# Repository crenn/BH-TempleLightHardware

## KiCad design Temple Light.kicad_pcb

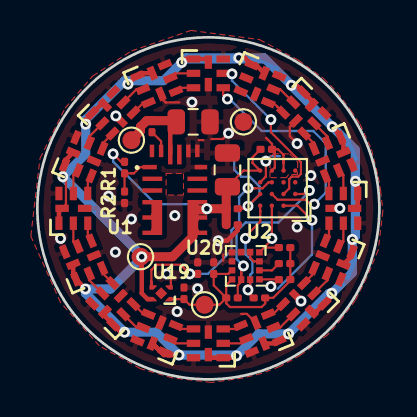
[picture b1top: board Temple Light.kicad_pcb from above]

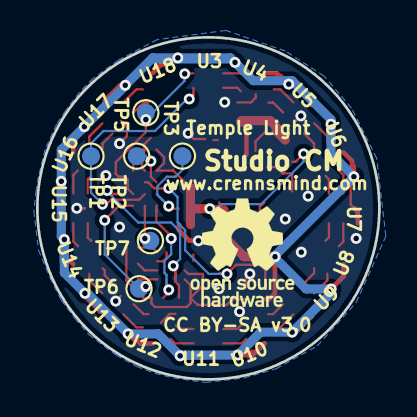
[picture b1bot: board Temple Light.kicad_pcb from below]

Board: 2 copper layers, 19.0 x 19.0 mm, 46 parts (6 on the bottom side), 47 nets.

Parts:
C1, C4, C5: 100NF; C_0201_0603Metric
C2: 10UF/25V; C_0805_2012Metric
C3: 47UF/6V3; C_0805_2012Metric
C6: 1UF; C_0201_0603Metric
R1, R3, R6, R7, R8, R9: 24K9; R_0201_0603Metric
R2, R4, R5: 4K7; R_0201_0603Metric
R10: 180K; R_0201_0603Metric
TP1, TP2, TP3, TP5, TP6, TP7, TP8, TP9, TP10, TP11: TestPoint; TestPoint_Pad_D1.0mm
U1: MPM3620
U2: ATtiny20-CCU; UFBGA-15_3.0x3.0mm_Layout4x4_P0.65mm
U3, U4, U5, U6, U7, U8, U9, U10, U11, U12, U13, U14, U15, U16, U17, U18: APA102-2020
U19: MIC5366-3.3; 4-TDFN 1.0x1.0mm
U20: LIS2DE12; LGA-12_2x2mm_P0.5mm

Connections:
+3V3: C5.1, C6.1, R4.1, R5.1, R6.1, R7.1, R9.1, TP10.1, U19.1, U20.9, U20.10
+5V: C1.1, C3.1, C4.1, R1.1, R3.1, TP9.1, U1.7, U1.8, U1.9, U2.D4, U3.1, U4.1, U5.1, U6.1, U7.1, U8.1, U9.1, U10.1, U11.1, U12.1, U13.1, U14.1, U15.1, U16.1, U17.1, U18.1, U19.4
+24V: C2.1, R10.2, TP8.1, U1.16
/CLOCK_8: U10.2, U11.5
/DATA_8: U10.3, U11.4
/EN: R8.1, U2.C3, U19.3
/INT0: R7.2, U2.A4, U20.12
/LED_CLK_IN: TP5.1, U2.B2, U3.5
/LED_DAT_IN: TP1.1, U2.B3, U3.4
/PCINT: R9.2, U2.B1, U20.11
/RESET: R3.2, TP3.1, U2.B4
/SCL: R4.2, TP6.1, U2.A2, U20.1
/SDA: R5.2, TP7.1, U2.A3, U20.4
/TPICLK: TP2.1, U2.C4
GND: C1.2, C2.2, C3.2, C4.2, C5.2, C6.2, R2.2, R8.2, TP11.1, U1.3, U1.12, U1.13, U1.14, U2.D2, U2.D3, U3.6, U4.6, U5.6, U6.6, U7.6, U8.6, U9.6, U10.6, U11.6, U12.6, U13.6, U14.6, U15.6, U16.6, U17.6, U18.6, U19.2, U20.3, U20.5, U20.6, U20.7, U20.8
unnamed: R1.2, R2.1, U1.1
unnamed: R6.2, U20.2
unnamed: R10.1, U1.17
unnamed: U1.4, U1.5, U1.6
unnamed: U3.2, U4.5
unnamed: U3.3, U4.4
unnamed: U4.2, U5.5
unnamed: U4.3, U5.4
unnamed: U5.2, U6.5
unnamed: U5.3, U6.4
unnamed: U6.2, U7.5
unnamed: U6.3, U7.4
unnamed: U7.2, U8.5
unnamed: U7.3, U8.4
unnamed: U8.2, U9.5
unnamed: U8.3, U9.4
unnamed: U9.3, U10.4
unnamed: U9.2, U10.5
unnamed: U11.2, U12.5
unnamed: U11.3, U12.4
unnamed: U12.2, U13.5
unnamed: U12.3, U13.4
unnamed: U13.2, U14.5
unnamed: U13.3, U14.4
unnamed: U14.2, U15.5
unnamed: U14.3, U15.4
unnamed: U15.2, U16.5
unnamed: U15.3, U16.4
unnamed: U16.2, U17.5
unnamed: U16.3, U17.4
unnamed: U17.2, U18.5
unnamed: U17.3, U18.4

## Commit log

2018-10-22 Version 0.1 Hardware
    Initial commit of the hardware done outside of version control.
2019-03-21 Fill out sch. title block, add pdf copy of schematic

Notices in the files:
Temple Light.kicad_pcb:
CC BY-SA v3.0
